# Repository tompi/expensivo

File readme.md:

Expensivo
=========

A wireless version of the [Cheapino](https://github.com/tompi/cheapino): same
shape and key layout, but with a nice!nano in each half, ZMK and Bluetooth
between the halves. Not quite as cheap anymore, hence the name.

- 36 keys (3x5 + 3 thumb keys per half), MX hotswap sockets
- every key has its own pin on the nice!nano: no diodes, no matrix
- one reversible PCB for both halves: the left half is built on the front,
  the right half on the back
- LiPo battery, power switch and reset button on each half
- optional EC11 encoder on the right half
- 3D-printed case with an optional magnetic cover over the nice!nano

Parts per keyboard
------------------

| Part | Qty | Notes |
|------|----:|-------|
| PCB | 2 | same board for both halves, see [Ordering the PCB](#ordering-the-pcb) |
| nice!nano v2 | 2 | or a compatible nRF52840 Pro Micro clone |
| Sockets + pins for the nice!nano | 2 sets | 12-pin single row; the case assumes the nano sits 4.9 mm above the PCB |
| LiPo battery | 2 | fits under the nano between the sockets, e.g. 301230 (3 x 12 x 30 mm); may stick out ~6 mm past the nano |
| MX switches | 36 | |
| Kailh MX hotswap sockets | 36 | MX, not low profile |
| Slide switch PCM12SMTR | 2 | one per half |
| Tactile switch TL3342 | 2 | reset, one per half |
| Keycaps | 36 | |
| EC11 encoder | 0-1 | optional, right half only |

For the case, per keyboard: 16 M2 heat-set inserts (4 mm long, 3 mm OD),
16 M2x5 countersunk screws, silicone bumpers (10 mm), 8 + 8 6x2 mm magnets
(8 in the bottom plates, 8 for the two covers).

Building it
-----------

The PCB is reversible, so it matters which side you solder on:

- **left half:** everything on the front side (the side marked LEFT);
  hotswap sockets on the back
- **right half:** everything on the back side (marked RIGHT); hotswap sockets on the front
- the nice!nano goes on the same side as its label, components facing up
- bridge the four solder jumpers next to the nano's top pins on the side the
  nano is on (marked "BRIDGE ALL 4"), and leave the other four open
- the power switch and reset button have a footprint on each side; fit only
  the one on top
- battery to the pads below the nano, + and - are marked

The [schematic](pcb/expensivo.kicad_sch) shows how it is wired, including
which nano pin ends up on which hole on each side.

Firmware
--------

ZMK, built by GitHub Actions on every push (see the Actions tab for the
`.uf2` files). The left half is the central and has ZMK Studio enabled.

- keymap: [config/expensivo.keymap](config/expensivo.keymap)
- shield: [zmk/boards/shields/expensivo](zmk/boards/shields/expensivo)

To flash, double-tap reset and copy the matching `.uf2` to the drive that
shows up. Flash `settings_reset` first if the nanos were used before.

Case
----

OpenSCAD files in [case/](case), see [case/readme.md](case/readme.md). The
top frames print top face down without supports, so do the covers; the
covers hold on with magnets and can be left off.

Ordering the PCB
----------------

`scripts/gerbers.sh` writes `build/expensivo-jlcpcb.zip`, ready for JLCPCB:
2 layers, 1.6 mm, default settings. 5 boards is two keyboards and a spare.
Choose ENIG if you want the copper logo to stay shiny.

How it's made
-------------

Everything is generated by scripts, so edit those rather than the outputs:

| Script | Makes |
|--------|-------|
| `scripts/build.sh` | the full board build: footprint, PCB, routing, DRC/ERC, schematic, case data |
| `scripts/build_pcb.py` | the PCB, starting from the Cheapino board: parts, nets, outline, logo |
| `scripts/gen_nano_footprint.py` | the reversible nice!nano footprint |
| `scripts/gen_schematic.py` | the schematic, from the PCB's parts and nets |
| `scripts/gen_zmk.py` | the ZMK shield pin lists |
| `scripts/gen_case.py` | PCB geometry for the OpenSCAD case |
| `scripts/gerbers.sh` | Gerbers and drill files for JLCPCB |

The pin map shared by the PCB, schematic and firmware is in
`scripts/layout.py`. Routing is done by Freerouting (downloaded on first run,
needs Java). The scripts expect KiCad 8 in `/Applications/KiCad`.

License
-------

This work is licensed under a [Creative Commons Attribution license.](LICENSE.txt)

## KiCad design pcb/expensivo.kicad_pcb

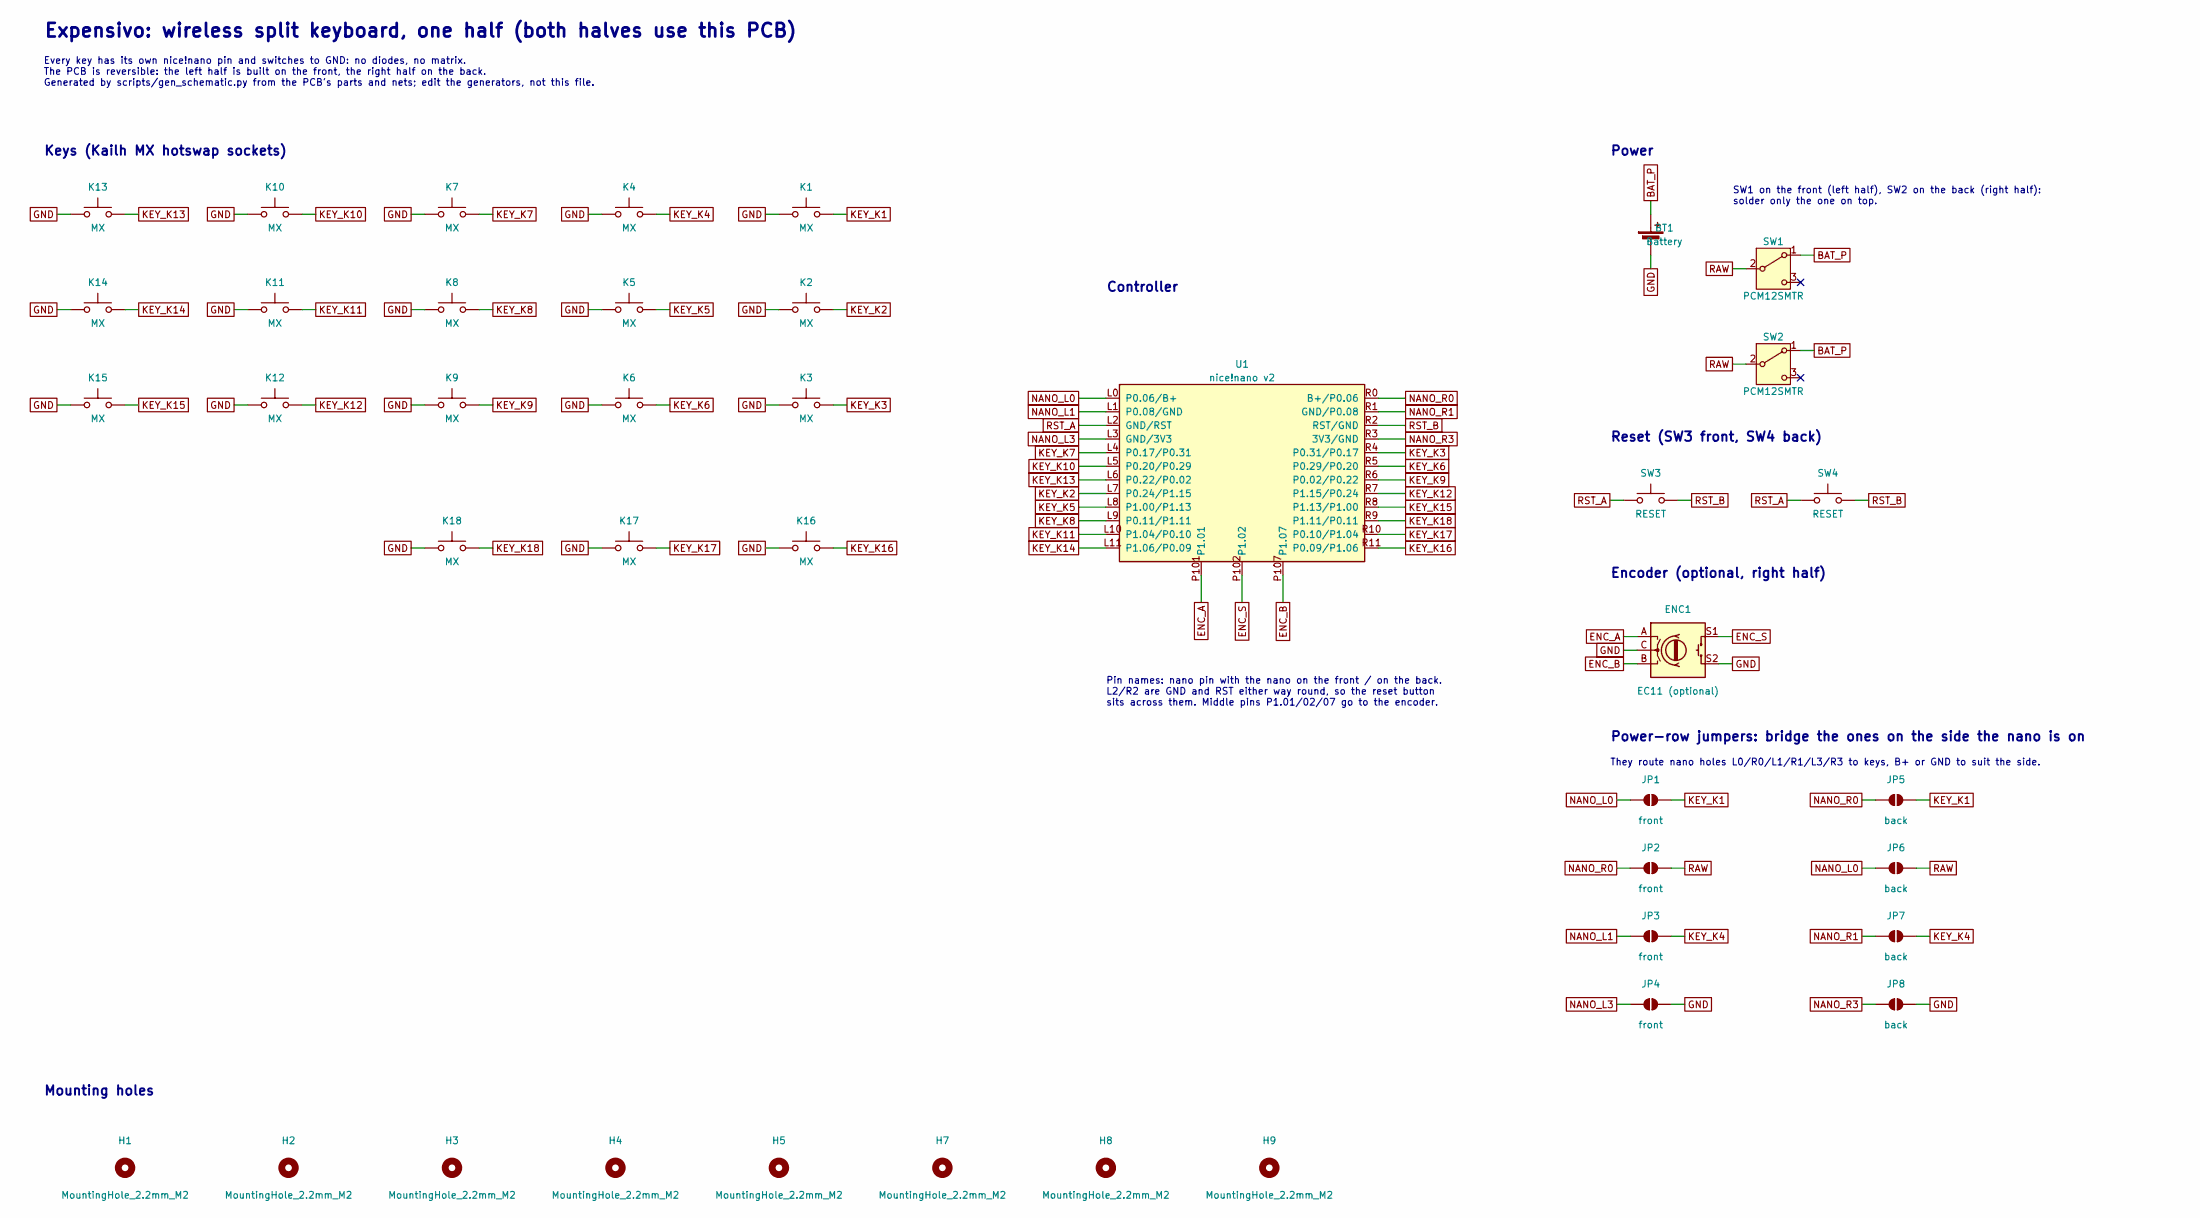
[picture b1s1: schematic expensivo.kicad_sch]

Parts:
BT1: Battery; PinHeader_1x02_P2.54mm_Vertical
ENC1: EC11 (optional); RotaryEncoder_Alps_EC11E-Switch_Vertical_H20mm
H1, H2, H3, H4, H5, H7, H8, H9: MountingHole_2.2mm_M2
JP1, JP2, JP3, JP4: front; SolderJumper-2_P1.3mm_Open_TrianglePad1.0x1.5mm
JP5, JP6, JP7, JP8: back; SolderJumper-2_P1.3mm_Open_TrianglePad1.0x1.5mm
K1, K2, K3, K4, K5, K6, K7, K8, K9, K10, K11, K12, K13, K14, K15, K16, K17, K18: MX; Kailh_socket_MX_optional_reversible
SW1, SW2: PCM12SMTR; SW_SPDT_PCM12
SW3, SW4: RESET; SW_SPST_TL3342
U1: nice!nano v2; nice_nano_reversible

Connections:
BAT_P: BT1.1 (+), SW1.1 (A), SW2.1 (A)
ENC_A: ENC1.A, U1.P101 (P1.01)
ENC_B: ENC1.B, U1.P107 (P1.07)
ENC_S: ENC1.S1, U1.P102 (P1.02)
GND: BT1.2 (-), ENC1.C, ENC1.S2, JP4.2 (B), JP8.2 (B), K1.1, K2.1, K3.1, K4.1, K5.1, K6.1, K7.1, K8.1, K9.1, K10.1, K11.1, K12.1, K13.1, K14.1, K15.1, K16.1, K17.1, K18.1
KEY_K1: JP1.2 (B), JP5.2 (B), K1.2
KEY_K2: K2.2, U1.L7 (P0.24/P1.15)
KEY_K3: K3.2, U1.R4 (P0.31/P0.17)
KEY_K4: JP3.2 (B), JP7.2 (B), K4.2
KEY_K5: K5.2, U1.L8 (P1.00/P1.13)
KEY_K6: K6.2, U1.R5 (P0.29/P0.20)
KEY_K7: K7.2, U1.L4 (P0.17/P0.31)
KEY_K8: K8.2, U1.L9 (P0.11/P1.11)
KEY_K9: K9.2, U1.R6 (P0.02/P0.22)
KEY_K10: K10.2, U1.L5 (P0.20/P0.29)
KEY_K11: K11.2, U1.L10 (P1.04/P0.10)
KEY_K12: K12.2, U1.R7 (P1.15/P0.24)
KEY_K13: K13.2, U1.L6 (P0.22/P0.02)
KEY_K14: K14.2, U1.L11 (P1.06/P0.09)
KEY_K15: K15.2, U1.R8 (P1.13/P1.00)
KEY_K16: K16.2, U1.R11 (P0.09/P1.06)
KEY_K17: K17.2, U1.R10 (P0.10/P1.04)
KEY_K18: K18.2, U1.R9 (P1.11/P0.11)
NANO_L0: JP1.1 (A), JP6.1 (A), U1.L0 (P0.06/B+)
NANO_L1: JP3.1 (A), U1.L1 (P0.08/GND)
NANO_L3: JP4.1 (A), U1.L3 (GND/3V3)
NANO_R0: JP2.1 (A), JP5.1 (A), U1.R0 (B+/P0.06)
NANO_R1: JP7.1 (A), U1.R1 (GND/P0.08)
NANO_R3: JP8.1 (A), U1.R3 (3V3/GND)
RAW: JP2.2 (B), JP6.2 (B), SW1.2 (B), SW2.2 (B)
RST_A: SW3.1, SW4.1, U1.L2 (GND/RST)
RST_B: SW3.2, SW4.2, U1.R2 (RST/GND)

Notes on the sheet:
Expensivo: wireless split keyboard, one half (both halves use this PCB)
Every key has its own nice!nano pin and switches to GND: no diodes, no matrix. The PCB is reversible: the left half is built on the front, the right half on the back. Generated by scripts/gen_schematic.py from the PCB's parts and nets; edit the generators, not this file.
Keys (Kailh MX hotswap sockets)
Controller
Pin names: nano pin with the nano on the front / on the back. L2/R2 are GND and RST either way round, so the reset button sits across them. Middle pins P1.01/02/07 go to the encoder.
Power
SW1 on the front (left half), SW2 on the back (right half): solder only the one on top.
Reset (SW3 front, SW4 back)
Encoder (optional, right half)
Power-row jumpers: bridge the ones on the side the nano is on
They route nano holes L0/R0/L1/R1/L3/R3 to keys, B+ or GND to suit the side.
Mounting holes

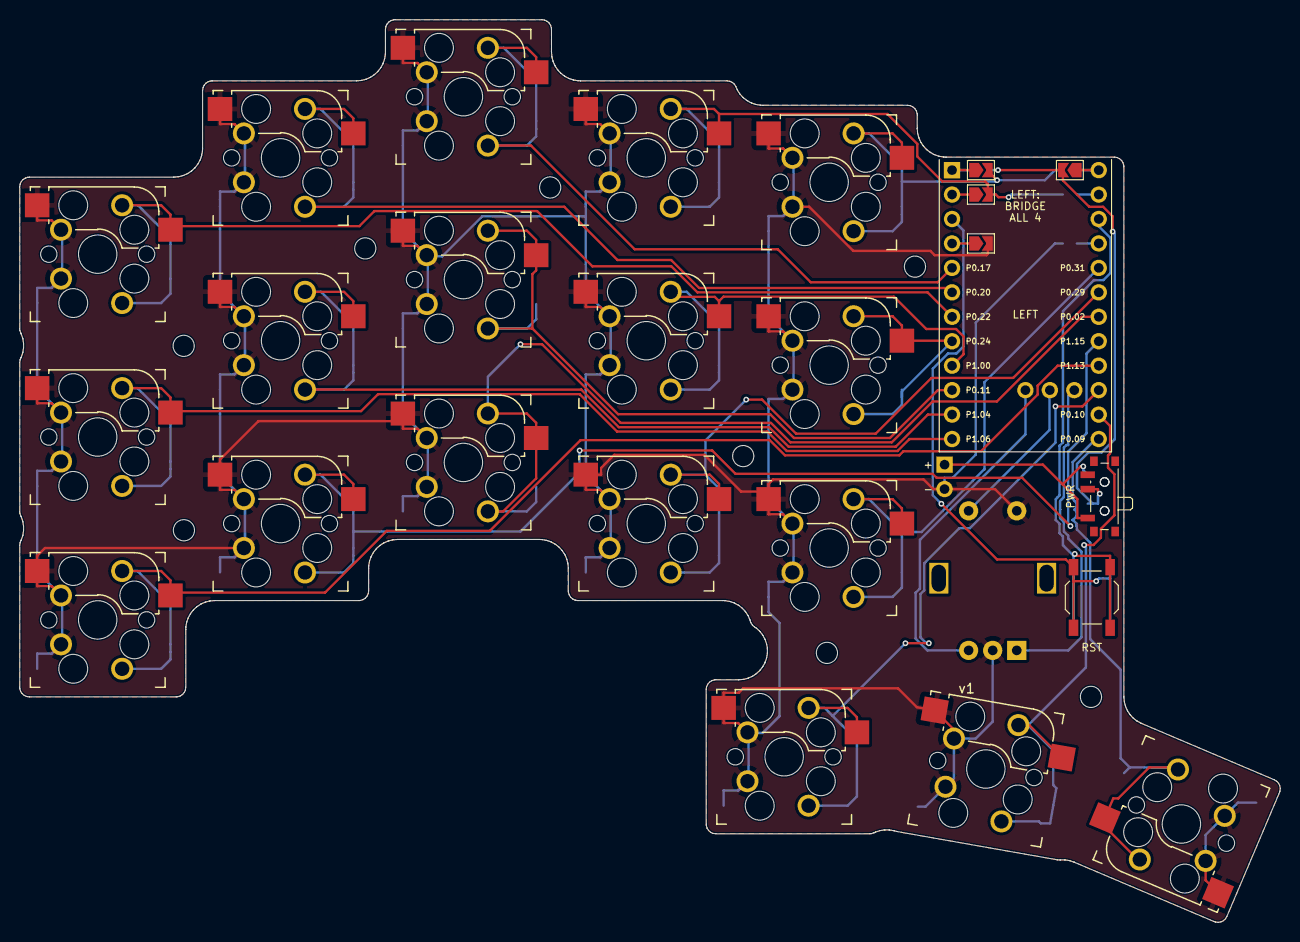
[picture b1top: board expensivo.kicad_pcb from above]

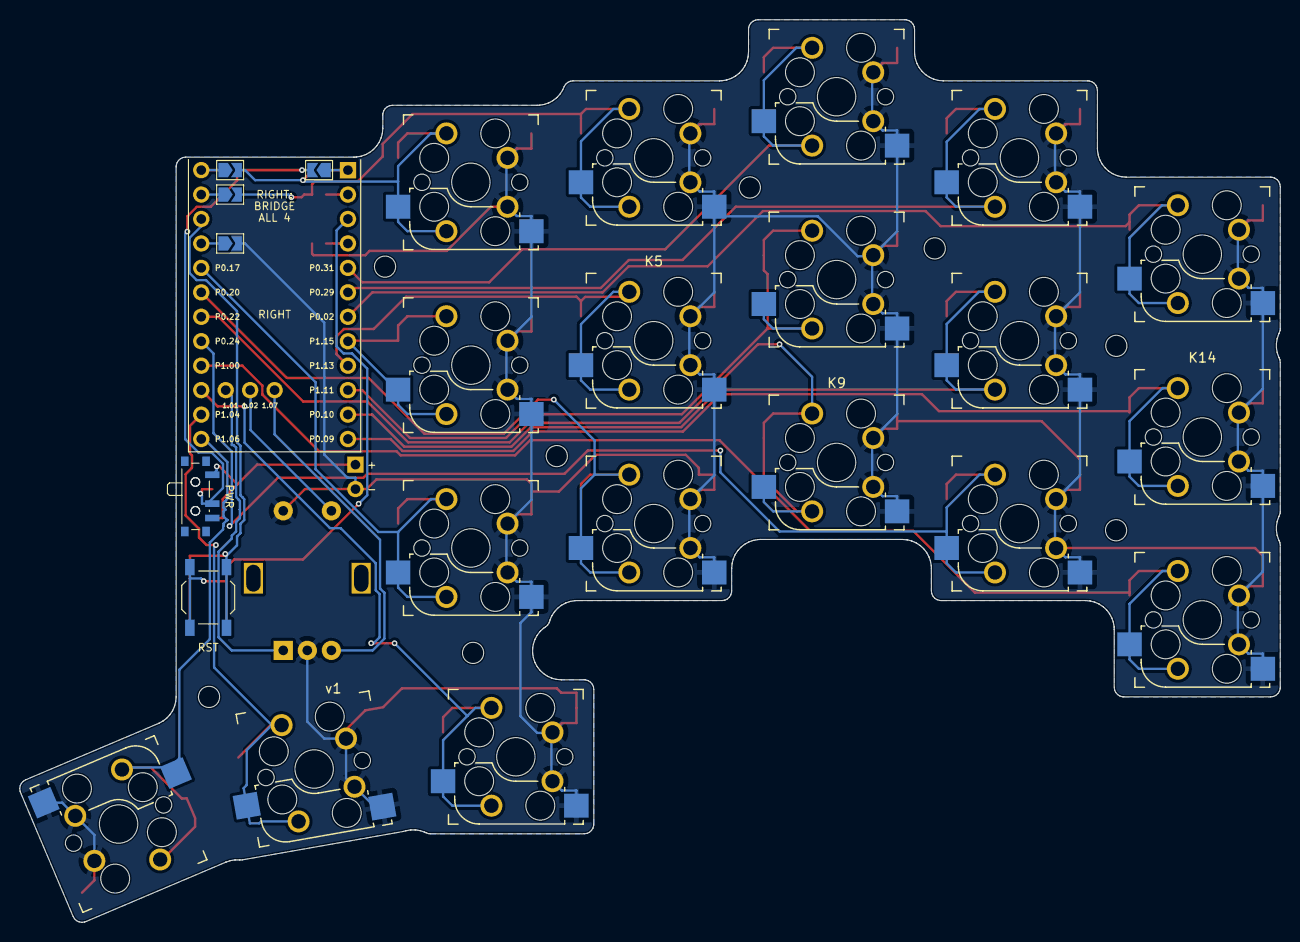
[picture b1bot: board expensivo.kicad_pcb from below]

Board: 2 copper layers, 131.0 x 93.8 mm, 41 parts (7 on the bottom side), 32 nets.

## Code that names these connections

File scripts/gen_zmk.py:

#!/usr/bin/env python3
"""Generate the expensivo ZMK shield pin lists from the PCB hole mapping."""
import os

from layout import KEY_ROWS, THUMBS, key_pins

ROOT = os.path.normpath(os.path.join(os.path.dirname(os.path.abspath(__file__)), ".."))
SHIELD = os.path.join(ROOT, "zmk", "boards", "shields", "expensivo")

# encoder pins, only wired on the right half (nano on the back)
ENC_A, ENC_B, ENC_S = "P1.01", "P1.07", "P1.02"


def gpio(pin, flags="GPIO_ACTIVE_LOW | GPIO_PULL_UP"):
    port, num = pin[1:].split(".")
    return f"<&gpio{port} {int(num)} ({flags})>"


def key_order(right):
    """Keys in keymap order for one half: rows, then thumbs, left to right."""
    rows = [list(reversed(r)) if right else r for r in KEY_ROWS]
    thumbs = list(reversed(THUMBS)) if right else THUMBS
    return [k for r in rows for k in r] + thumbs


def overlay(right):
    pins = key_pins(back=right)
    keys = key_order(right)
    lines = [f"            {'= ' if i == 0 else ', '}{gpio(pins[k])} // {k}" for i, k in enumerate(keys)]
    if right:
        lines.append(f"            , {gpio(ENC_S)} // encoder push")
    out = ["// Generated by scripts/gen_zmk.py -- edit the generator, not this file.",
           '#include "expensivo.dtsi"', ""]
    if right:
        out += ["&default_transform {", "    col-offset = <18>;", "};", "",
                "&encoder {", "    status = \"okay\";", "};", ""]
    out += ["&kscan0 {", "    input-gpios", *lines, "            ;", "};", ""]
    return "\n".join(out)


def dtsi():
    rows = []
    for r in range(3):
        l = " ".join(f"RC(0,{r * 5 + c})" for c in range(5))
        rr = " ".join(f"RC(0,{18 + r * 5 + c})" for c in range(5))
        rows.append(f"            {l}    {rr}")
    rows.append("                            RC(0,15) RC(0,16) RC(0,17)    "
                "RC(0,33) RC(0,34) RC(0,35)   RC(0,36)")
    return f"""// Generated by scripts/gen_zmk.py -- edit the generator, not this file.
#include <dt-bindings/zmk/matrix_transform.h>
#include "expensivo-layout.dtsi"

// P0.09 / P0.10 are used as key inputs
&uicr {{
    nfct-pins-as-gpios;
}};

&expensivo_layout {{
    transform = <&default_transform>;
}};

/ {{
    chosen {{
        zmk,kscan = &kscan0;
        zmk,physical-layout = &expensivo_layout;
    }};

    default_transform: keymap_transform_0 {{
        compatible = "zmk,matrix-transform";
        columns = <37>;
        rows = <1>;
        // last entry is the (optional) encoder push on the right half
        map = <
{chr(10).join(rows)}
        >;
    }};

    kscan0: kscan {{
        compatible = "zmk,kscan-gpio-direct";
        wakeup-source;
    }};

    encoder: encoder {{
        compatible = "alps,ec11";
        a-gpios = {gpio(ENC_A, "GPIO_ACTIVE_HIGH | GPIO_PULL_UP")};
        b-gpios = {gpio(ENC_B, "GPIO_ACTIVE_HIGH | GPIO_PULL_UP")};
        steps = <80>;
        status = "disabled";
    }};

    sensors: sensors {{
        compatible = "zmk,keymap-sensors";
        sensors = <&encoder>;
        triggers-per-rotation = <20>;
    }};
}};
"""


def main():
    os.makedirs(SHIELD, exist_ok=True)
    files = {
        "expensivo.dtsi": dtsi(),
        "expensivo_left.overlay": overlay(False),
        "expensivo_right.overlay": overlay(True),
    }
    for name, text in files.items():
        with open(os.path.join(SHIELD, name), "w") as f:
            f.write(text)
        print("wrote", name)


if __name__ == "__main__":
    main()
